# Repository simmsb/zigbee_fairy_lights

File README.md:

# Esp32 battery powered Zigbee fairy lights

A little thing I threw together this christmas.

It uses a DFRobot firebeetle2 esp32c6 as a zigbee end device, which is then used
to manage the output of a LED driver.

This is then used to power some outdoor fairy lights.

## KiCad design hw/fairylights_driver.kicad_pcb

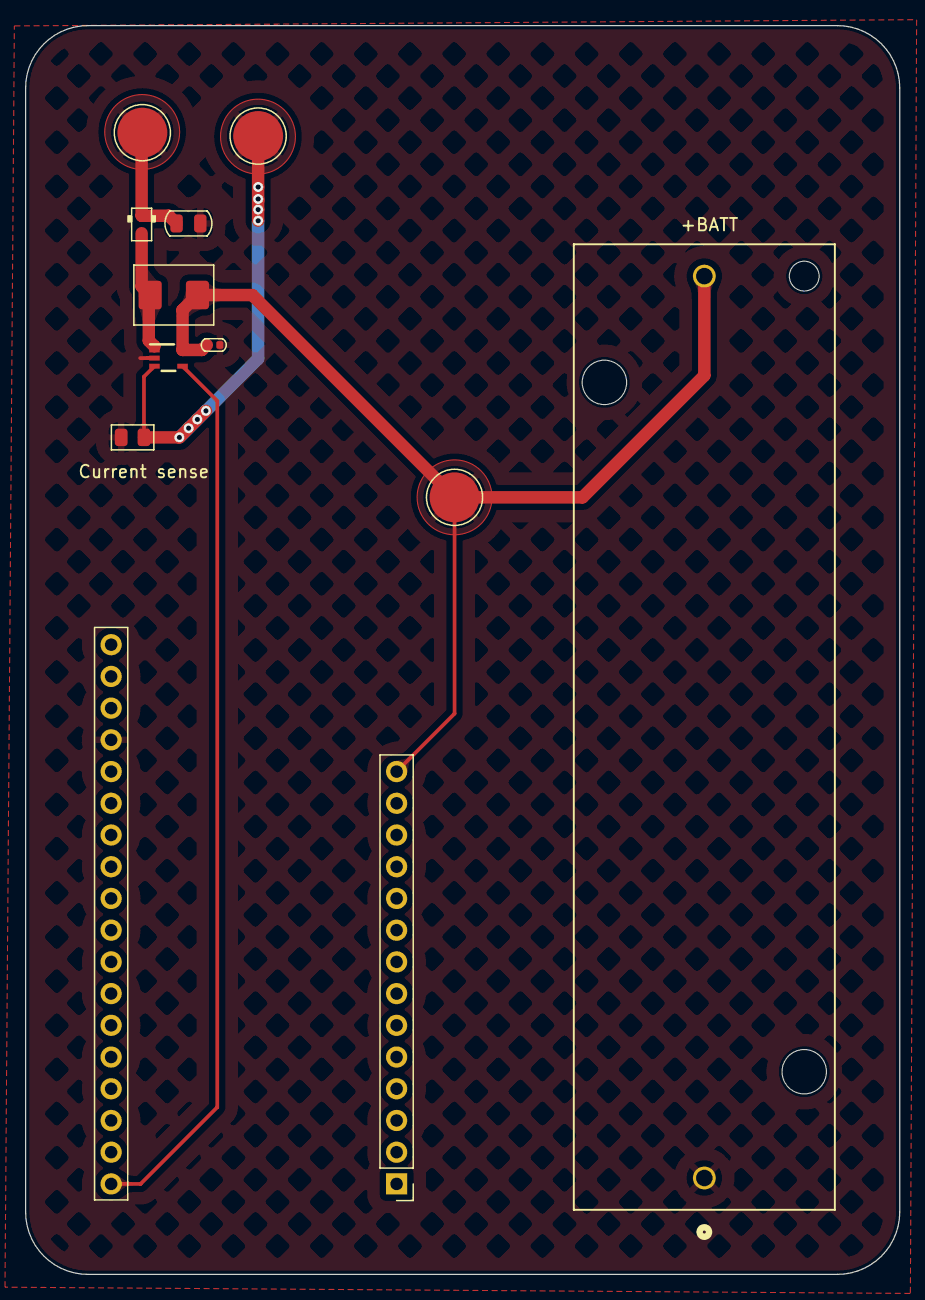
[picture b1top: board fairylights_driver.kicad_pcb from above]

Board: 2 copper layers, 70.0 x 100.0 mm, 11 parts (0 on the bottom side), 6 nets.

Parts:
B1: 1043P; BATT_1043P_KEY
C2: 4.7uF; C_0402_1005Metric
C3: 1uF; C_0805_2012Metric
D1: D_Schottky_Generic; D_SOD-523
J1: +LED; TestPoint_Pad_D4.0mm
J2: -LED; TestPoint_Pad_D4.0mm
J3: VIN; TestPoint_Pad_D4.0mm
L1: IHLP1616BZER4R7M11; L_Vishay_IHLP-1616
R2: 5.1; R_0805_2012Metric
U1: firebeetle2
U2: TPS61169DCKR; DCK0005A_N

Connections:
/ctrl: U1.15 (PA17), U2.4 (CTRL)
/vin: B1.2, C2.1, J3.1, L1.1, U1.14 (VIN), U2.5 (VIN)
GND: B1.1, C2.2, C3.2, R2.2, U1.29 (GND), U2.2 (GND)
unnamed: D1.2 (A), L1.2, U2.1 (SW)
unnamed: C3.1, D1.1 (K), J1.1
unnamed: J2.1, R2.1, U2.3 (FB)

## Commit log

2024-12-24 fix adc: reinitialise it each time
2025-01-05 Bump deps
2025-01-05 Actually fix adc after sleep
